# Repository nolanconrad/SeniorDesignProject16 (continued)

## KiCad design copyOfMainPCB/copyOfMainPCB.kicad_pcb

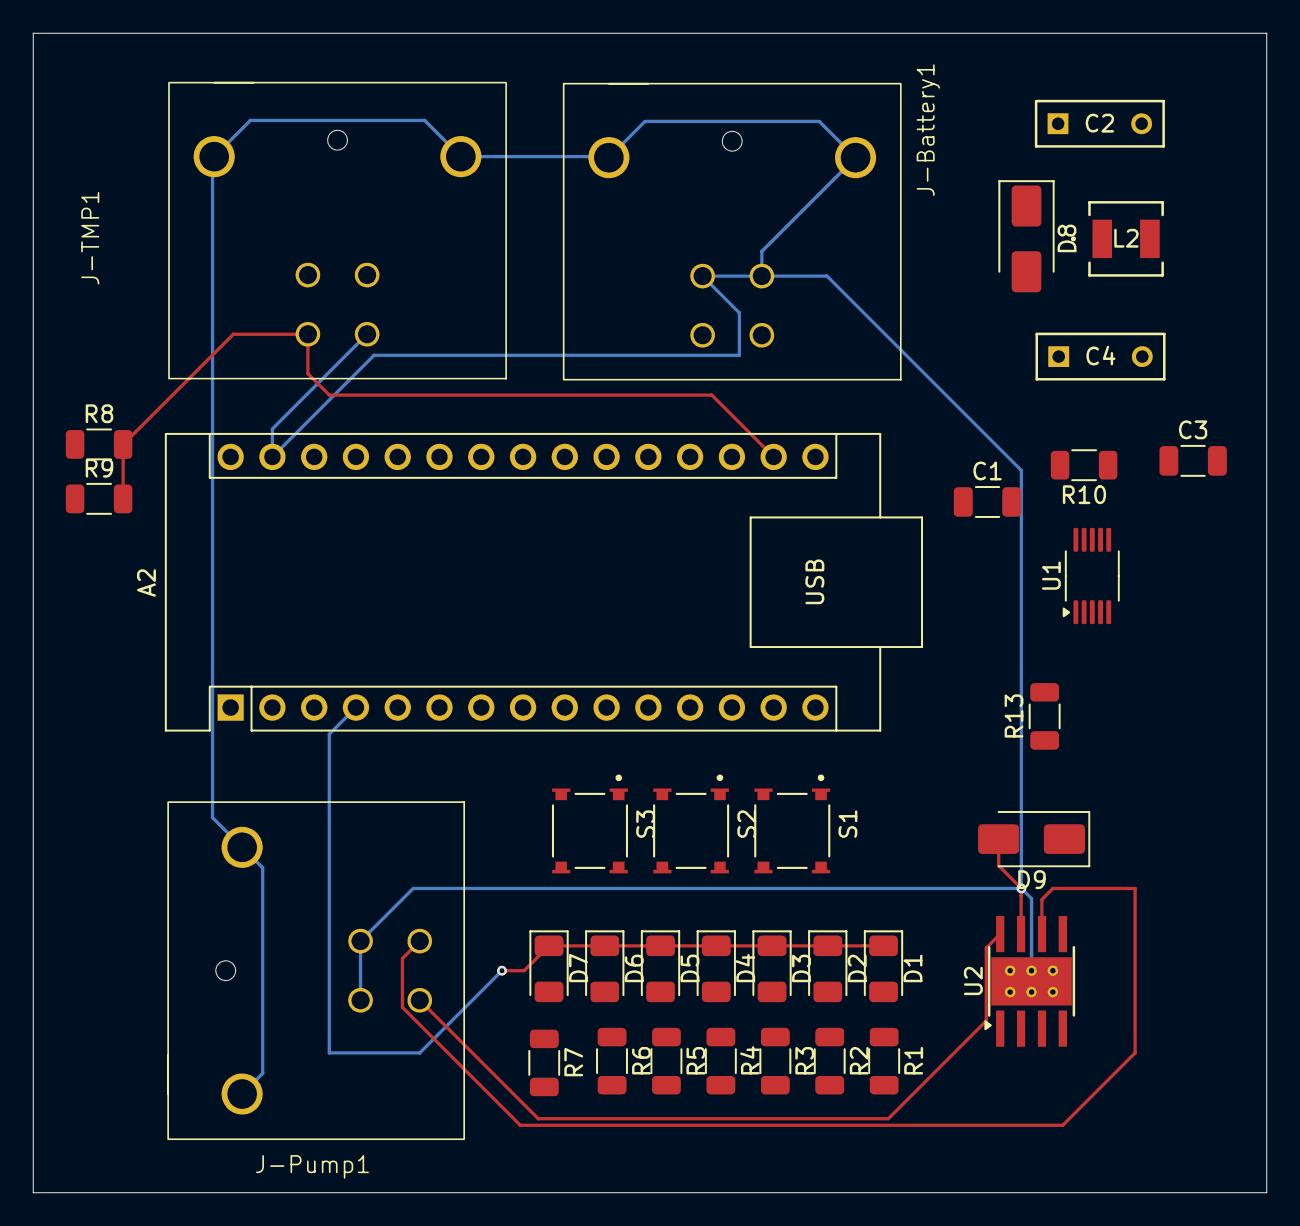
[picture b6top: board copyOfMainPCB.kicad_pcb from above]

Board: 2 copper layers, 75.0 x 70.5 mm, 34 parts (0 on the bottom side), 30 nets.

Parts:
A2: Arduino_Nano_ESP32; Arduino_Nano
C1: 10uF; C_1206_3216Metric
C2, C4: BQ014E0473J; CAP_BF01_AVX
C3: 0.1uF; C_1206_3216Metric
D1: LED Auto; LED_1206_3216Metric
D2: BAT3; LED_1206_3216Metric
D3: BAT2; LED_1206_3216Metric
D4: BAT1; LED_1206_3216Metric
D5: MAN 3; LED_1206_3216Metric
D6: MAN 2; LED_1206_3216Metric
D7: MAN 1; LED_1206_3216Metric
D8, D9: US1M; D_SMA
J-Battery1: 861-004-213R00Y
J-Pump1: 861-004-213R00Y
J-TMP1: 861-004-213R00Y
L2: LQH44PH220MPRL; IND_LQH44PN_PR_MUR-L
R1, R2, R3, R4, R5, R6, R7: 220; R_1206_3216Metric
R8, R9: 2.2k; R_1206_3216Metric
R10: 100m; R_1206_3216Metric
R13: 32k; R_1206_3216Metric
S1, S2, S3: TL3315NF250Q; SW_TL3315NF250Q
U1: INA226; VSSOP-10_3x3mm_P0.5mm
U2: DRV8871DDA; Texas_HTSOP-8-1EP_3.9x4.9mm_P1.27mm_EP2.95x4.9mm_Mask2.4x3.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

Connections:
+3.3V: A2.17 (3V3), C1.2, C3.2, J-TMP1.2, R8.2, R9.2, U1.6 (VS)
+BATT: D8.2 (A), J-Battery1.1, J-Battery1.2, R10.1, U1.10 (Vin+)
DRV: J-Pump1.1, U2.6 (OUT1)
GND: A2.4 (GND), A2.29 (GND), C1.1, C2.2, C3.1, C4.2, D1.1 (K), D2.1 (K), D3.1 (K), D4.1 (K), D5.1 (K), D6.1 (K), D7.1 (K), D9.2 (A), J-Battery1.3, J-Pump1.3, J-Pump1.4, J-TMP1.1, R13.2, S1.3, S1.4, S2.3, S2.4, S3.1, S3.2, U1.1 (A1), U1.2 (A0), U1.7 (GND), U2.1 (GND), U2.2 (IN2), U2.7 (GND), U2.9 (GND)
GNDPWR: J-Battery1.4, J-Battery1.SH1 (SHIELD), J-Battery1.SH2 (SHIELD__1), J-Pump1.SH1 (SHIELD), J-Pump1.SH2 (SHIELD__1), J-TMP1.SH1 (SHIELD), J-TMP1.SH2 (SHIELD__1), U2.9 (GND)
unnamed: A2.21 (A2), S1.1, S1.2
unnamed: A2.22 (A3), S2.1, S2.2
unnamed: A2.5 (D2), S3.3, S3.4
unnamed: A2.6 (D3), R1.1
unnamed: A2.7 (D4), R7.1
unnamed: A2.8 (D5), R6.1
unnamed: A2.9 (D6), R5.1
unnamed: A2.10 (D7), R4.1
unnamed: A2.11 (D8), R3.1
unnamed: A2.12 (D9), R2.1
unnamed: A2.30 (VIN), C2.1, L2.2
unnamed: D1.2 (A), R1.2
unnamed: D2.2 (A), R2.2
unnamed: D3.2 (A), R3.2
unnamed: D4.2 (A), R4.2
unnamed: D5.2 (A), R5.2
unnamed: D6.2 (A), R6.2
unnamed: D7.2 (A), R7.2
unnamed: C4.1, D8.1 (K), L2.1
unnamed: R13.1, U2.4 (ILIM)
PWM: A2.20 (A1), U2.3 (IN1)
RTN: J-Pump1.2, U2.8 (OUT2)
SCL: A2.24 (SCL/A5), J-TMP1.4, R9.1, U1.5 (SCL)
SDA: A2.23 (SDA/A4), J-TMP1.3, R8.1, U1.4 (SDA)
Vdrive: D9.1 (K), R10.2, U1.8 (Vbus), U1.9 (Vin-), U2.5 (VM)

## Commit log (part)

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2025-10-24 Phase 1
2025-10-24 wanted to test
2025-10-24 lots of jazz
2025-11-05 testing github
2025-11-09 made a new main file
2025-11-09 Motor.cpp is a test file for the motor only. MotorXcurrentSensor demonstrates the two in conjunction. It still needs work. main2.cpp runs the thermistors, its in celcius, so it also needs work.
2025-11-10 kicad pcb
2025-11-11 Hella shitake 11/10
2025-11-11 Stuff from 11/11
2025-11-12 LCD display
2025-11-12 Minor updates to both files
2025-11-13 updated LCD code
2025-11-14 more stuff
2025-11-14 updated Platform io
2025-11-14 Need to fix the progression
2025-11-15 added millis control
2025-11-17 worked on current sensor issue. LCD seems fine from code standpoint
2025-11-17 printing temps
2025-11-17 alarm set up
2025-11-17 changed to farenheight
2025-11-17 Nate Change
2025-11-17 Nate
2025-11-17 alarm code will add to main file if works
2025-11-17 just the temperature
2025-11-17 readd current after fix
2025-11-17 with delay
2025-11-17 new main edits
2025-11-17 more
2025-11-17 more main changes
2025-11-17 chat fixed lol
2025-11-18 revamped alarm code, and added implementations
2025-11-18 commented more stuff out. Made minimal changes.
2025-11-19 Updated the current sensor set up
2025-11-19 currentsensworks
2025-11-19 joshcode
2025-11-19 changedmotor
2025-11-19 STAY IN MAIN_FINAL
2025-11-19 newest newest
2025-11-19 made micah "branch"
2025-11-19 run micah code
2025-11-19 round 2
2025-11-19 pls pls make this final
2026-01-29 TMP PCB
2026-02-07 main
2026-02-09 nolan
2026-02-10 new stuff from 2.9
2026-02-10 2/9/26
2026-02-14 2/13
2026-02-16 i made a new branch to develop the i2c module
2026-02-19 did this on 2.17
2026-02-19 micah - WORK OUT OF IRR-DEV
2026-02-19 i think i2c is officailly done
2026-02-19 a couple further updates
2026-02-19 began support for pump operation module
2026-02-19 working on pump operation
2026-02-19 made some updates to the i2c module for error checking
2026-02-20 temporary temp check
2026-02-20 so much stuff but I think its good enough for today
2026-02-20 reconnect
2026-02-26 made a copy of the schematic
2026-03-06 nolan made a new PCB design
2026-03-09 not sure what was here
2026-03-09 changed the individual i2c stuff
2026-03-09 got the layout and routing just about finished
2026-03-10 DRV8871
2026-03-11 hella changes
2026-03-13 Layout
2026-03-13 3/13
2026-03-16 Almost done
2026-03-16 Done
2026-03-19 sorry for delay here's more pump operation
2026-03-19 REV2
2026-03-22 commiting this now so it doesnt drop off later
2026-03-24 3/23
2026-03-24 currently the LED's, buttons, and tmp's all work as they should.
2026-03-24 one last file
2026-03-27 added INA and DRV modules
2026-04-06 client ble without serial
2026-04-06 even more fleshed out client side
2026-04-08 Rev3
2026-04-08 NORA
2026-04-10 here with uuids
2026-04-10 so much
2026-04-13 the PWM timing stuff
2026-04-13 it built
2026-04-13 chnages for implicit declaration
2026-04-13 ble works and fixed i2c errors!
2026-04-13 Working version before tmp and INA changes
2026-04-13 the INA's are averaged and the system is working pretty well.
2026-04-17 4/17 main, which runs all systems (pump, auto, manual, temp sens) NO current sense added back in yet.
2026-04-17 finished(ish) code
2026-04-17 resolved merge conflicts + added ble to main code
2026-04-17 all i had time for might need more changes flash first
2026-04-18 4/18 - All systems work from a software standpoint
2026-04-23 latest design
2026-04-27 Final
2026-04-28 every sloppy bit thus far
2026-05-01 BLE WORKS WITH APP LETS GOOOOOO
2026-05-01 takes average of tmps
2026-05-04 added git ignore
2026-05-06 final code
2026-05-06 sorry final final code
